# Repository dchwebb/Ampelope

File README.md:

# Ampelope

Overview
--------

Ampelope is a four-channel combined envelope and VCA Eurorack module incorporating a tremolo effect. Each channel can be switched between a fast envelope time, a slow envelope time or a slow envelope with a sine tremolo modulating volume.

The envelopes are loosely modelled on an analog envelope (Roland System 100 type circuit) and feature analog correct capacitor charge/discharge characteristics.

Channels 1 and 2 share the same Attack/Decay/Sustain/Release (ADSR) controls, as do channels 3 and 4. This makes the module particularly suited to dual stereo operation. However each channel has its own gate control allowing independent control of four signals.

The gate controls are normalled in a cascade configuration. For example in dual stereo use gate 1 will be normalled to gate 2 and then a separate gate applied to channel 3 will control channels 3 and 4. In addition gate 1 is normalled to the Doepfer standard gate signal on the 16 pin Eurorack header.

The tremolo control can be clocked or free-run. When clocked the Tremolo potentiometer sets the speed of the tremolo to a multiple of the clock. The tremolo effect applies a sine wave modulation to the envelope.

In addition to the envlopes internal connection to the VCA, envelopes 1 and 3 are available on the front panel and envelopes 2 and 4 on a pin header on the back.

Technical
---------

The module is controlled by an STM32G431 microcontroller which contains four 12-bit DACs. These are used to generate the four envelopes.

The MCU runs at 170MHz and the envelopes samples are generated at 48kHz. The front panel potentiometers are digitised using the MCU's internal ADC. The MCU features a hardware CORDIC peripheral which is used to generate the exponential curves used to model an analog envelopes capacitor charge/discharge characteristics. The CORDIC co-processor is also used to generate the tremolo sine wave.

The MCU's USB peripheral is also connected on the reverse for configuration and upgrade purposes.

The VCA used is an Alpha AS3364 quad linear VCA IC (https://www.alfarzpp.lv/eng/sc/AS3364.php). The MCU outputs the envelopes via its internal DACs at 0V to 3.3V range. This is scaled to 0V to 2V which is the VCA fully closed/fully open range. The envelopes are also amplified to 0V to 8V for control of external modules.

Three TL074 op-amps handle buffering and amplification. NPN transistors provide voltage limiting to incoming gates. The power supply uses a linear regulator to generate the 3.3V digital and analog voltages used by the MCU.

Construction
------------

The module uses a 3 stacked PCB configuration. The components sit on a 4-layer daughter board connected with headers to the 2 layer control PCB holding the LEDs, potentiometers, switches and sockets. This is then bolted to the front panel, also constructed as a 2 layer PCB.

All schematic and PCB layout carried out in Kicad version 5.99.

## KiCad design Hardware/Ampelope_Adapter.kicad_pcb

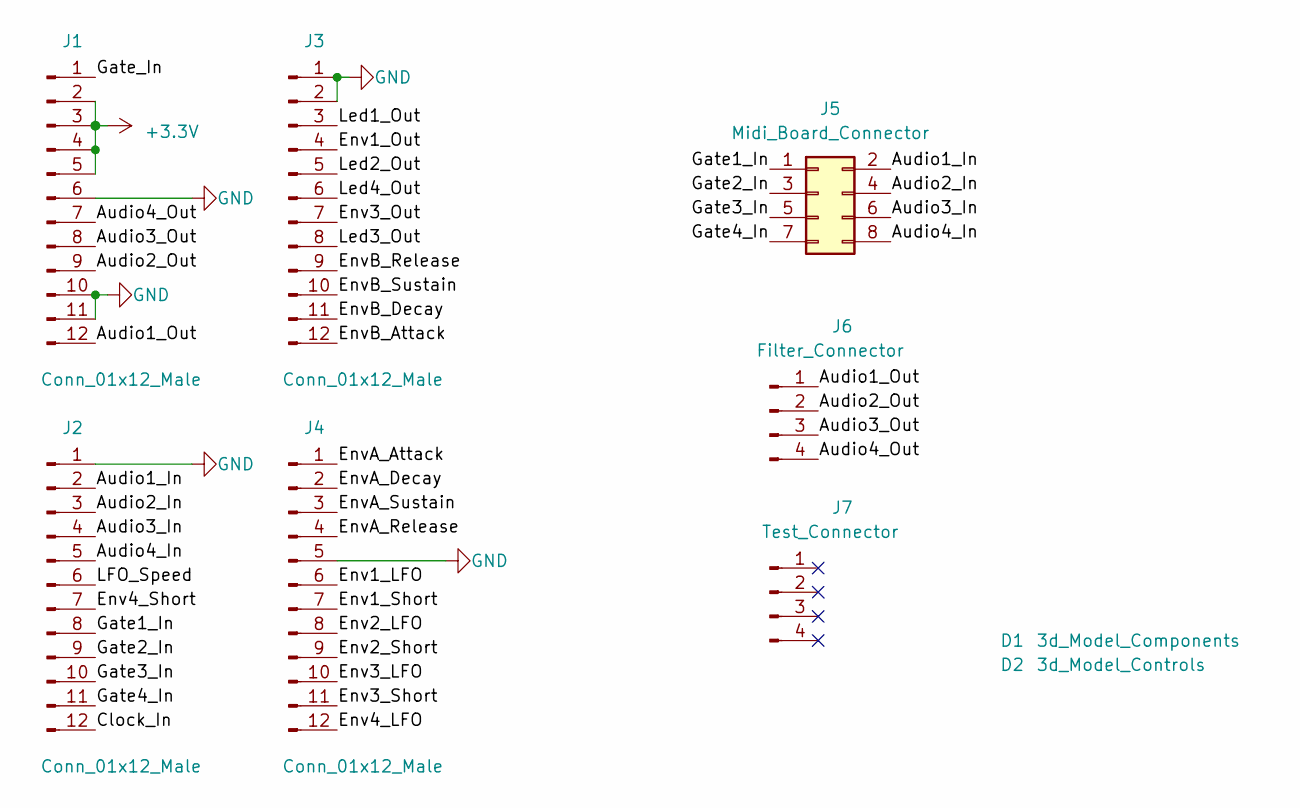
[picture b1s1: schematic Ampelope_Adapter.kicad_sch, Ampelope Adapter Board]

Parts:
D1: 3d_Model_Components; 3D_Dummy
D2: 3d_Model_Controls; 3D_Dummy
J1, J2, J3, J4: Conn_01x12_Male; PinSocket_1x12_P2.54mm_Vertical
J5: Midi_Board_Connector; PinHeader_2x04_P2.54mm_Vertical
J6: Filter_Connector; PinHeader_1x04_P2.54mm_Vertical
J7: Test_Connector; PinHeader_1x04_P2.54mm_Vertical

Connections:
+3V3: J1.2, J1.3, J1.4, J1.5
/Audio1_In: J2.2, J5.2
/Audio1_Out: J1.12, J6.1
/Audio2_In: J2.3, J5.4
/Audio2_Out: J1.9, J6.2
/Audio3_In: J2.4, J5.6
/Audio3_Out: J1.8, J6.3
/Audio4_In: J2.5, J5.8
/Audio4_Out: J1.7, J6.4
/Clock_In: J2.12
/Env1_LFO: J4.6
/Env1_Out: J3.4
/Env1_Short: J4.7
/Env2_LFO: J4.8
/Env2_Short: J4.9
/Env3_LFO: J4.10
/Env3_Out: J3.7
/Env3_Short: J4.11
/Env4_LFO: J4.12
/Env4_Short: J2.7
/EnvA_Attack: J4.1
/EnvA_Decay: J4.2
/EnvA_Release: J4.4
/EnvA_Sustain: J4.3
/EnvB_Attack: J3.12
/EnvB_Decay: J3.11
/EnvB_Release: J3.9
/EnvB_Sustain: J3.10
/Gate1_In: J2.8, J5.1
/Gate2_In: J2.9, J5.3
/Gate3_In: J2.10, J5.5
/Gate4_In: J2.11, J5.7
/Gate_In: J1.1
/LFO_Speed: J2.6
/Led1_Out: J3.3
/Led2_Out: J3.5
/Led3_Out: J3.8
/Led4_Out: J3.6
GND: J1.6, J1.10, J1.11, J2.1, J3.1, J3.2, J4.5

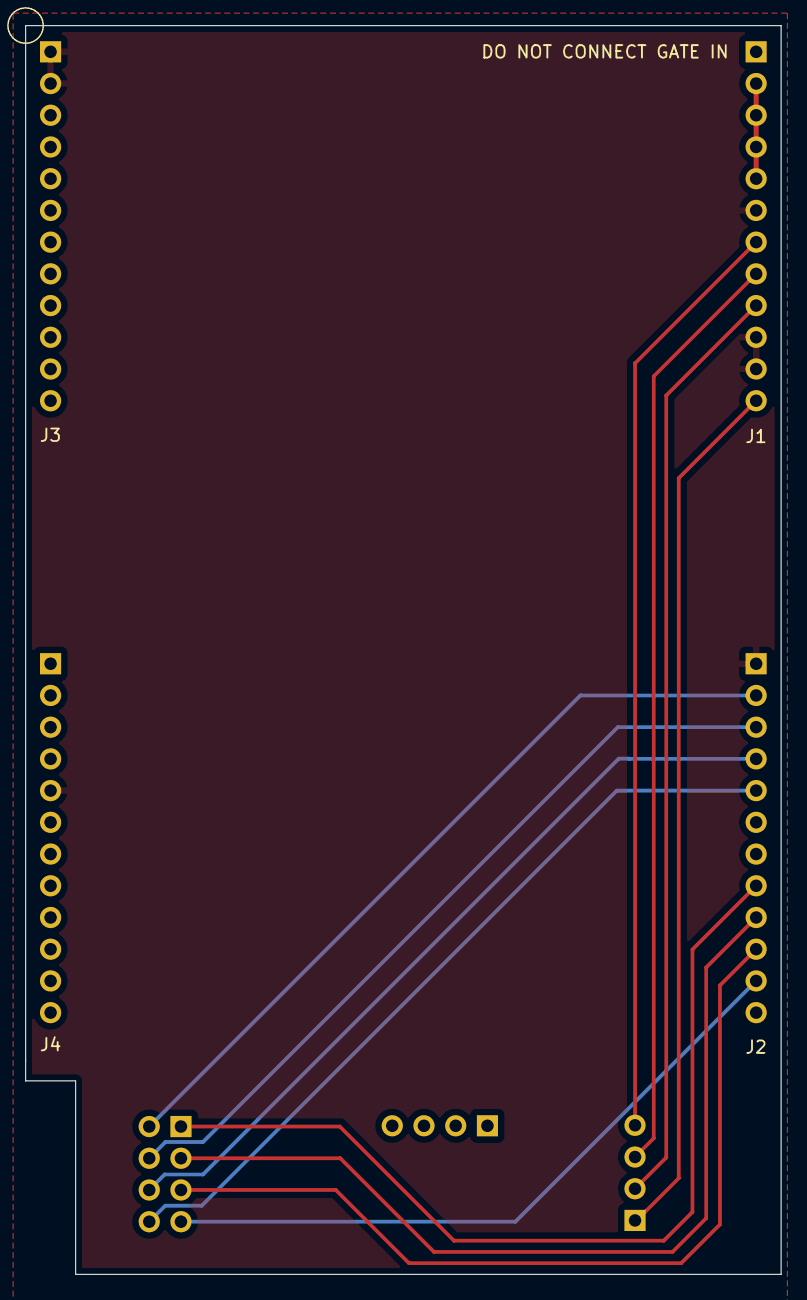
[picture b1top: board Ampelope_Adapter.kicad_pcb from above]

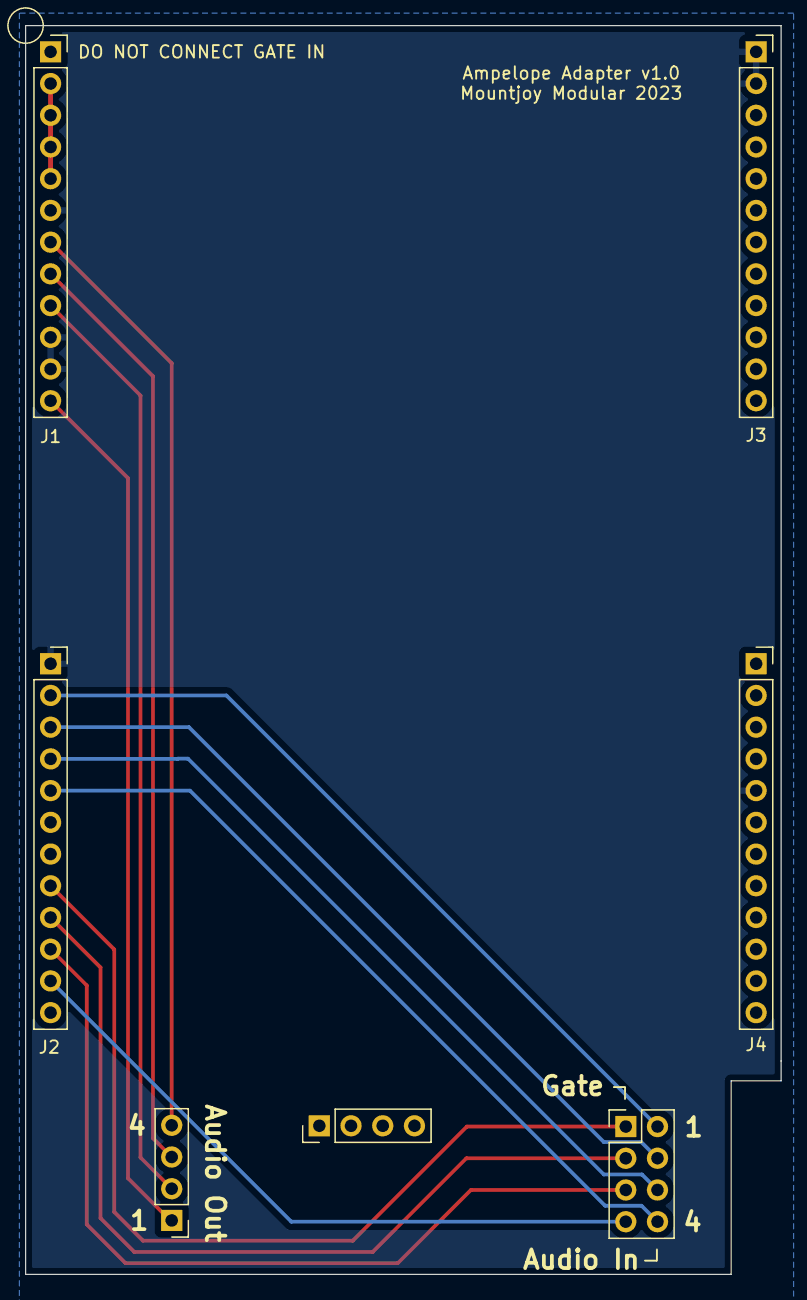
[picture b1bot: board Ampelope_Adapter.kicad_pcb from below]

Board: 2 copper layers, 60.5 x 100.0 mm, 9 parts (8 on the bottom side), 14 nets.

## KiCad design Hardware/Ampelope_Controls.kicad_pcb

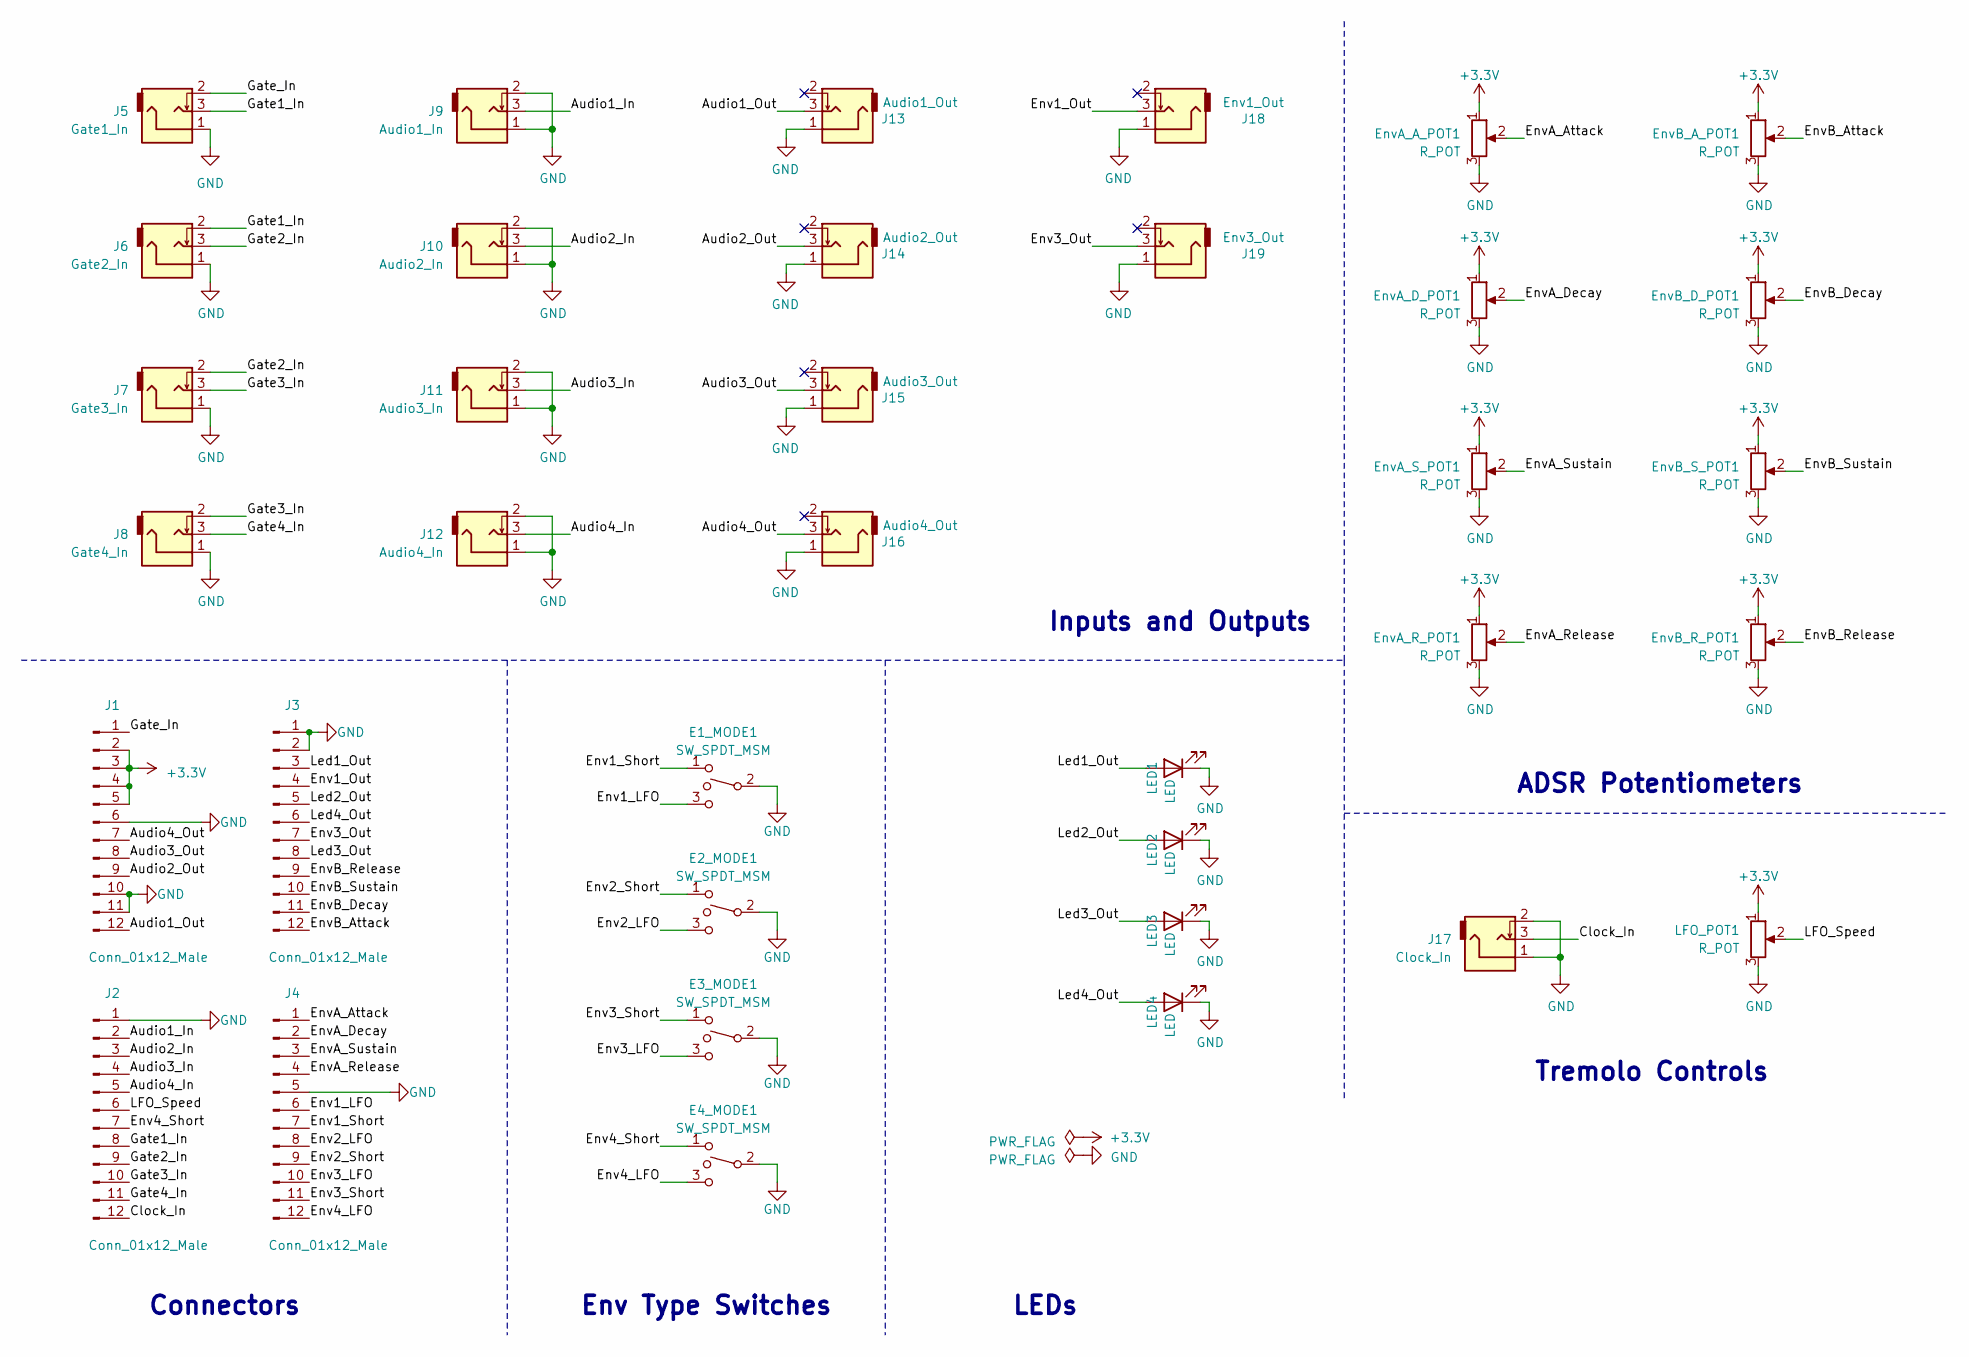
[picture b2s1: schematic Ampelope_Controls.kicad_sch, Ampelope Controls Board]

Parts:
E1_MODE1, E2_MODE1, E3_MODE1, E4_MODE1: SW_SPDT_MSM; SPDT_SubMiniature_Aligned
EnvA_A_POT1: R_POT; Alpha_9mm_Potentiometer_Aligned
EnvA_D_POT1: R_POT; Alpha_9mm_Potentiometer_Aligned
EnvA_R_POT1: R_POT; Alpha_9mm_Potentiometer_Aligned
EnvA_S_POT1: R_POT; Alpha_9mm_Potentiometer_Aligned
EnvB_A_POT1: R_POT; Alpha_9mm_Potentiometer_Aligned
EnvB_D_POT1: R_POT; Alpha_9mm_Potentiometer_Aligned
EnvB_R_POT1: R_POT; Alpha_9mm_Potentiometer_Aligned
EnvB_S_POT1: R_POT; Alpha_9mm_Potentiometer_Aligned
J1, J2, J3, J4: Conn_01x12_Male; PinHeader_1x12_P2.54mm_Vertical
J5: Gate1_In; THONKICONN_hole
J6: Gate2_In; THONKICONN_hole
J7: Gate3_In; THONKICONN_hole
J8: Gate4_In; THONKICONN_hole
J9: Audio1_In; THONKICONN_hole
J10: Audio2_In; THONKICONN_hole
J11: Audio3_In; THONKICONN_hole
J12: Audio4_In; THONKICONN_hole
J13: Audio1_Out; THONKICONN_hole
J14: Audio2_Out; THONKICONN_hole
J15: Audio3_Out; THONKICONN_hole
J16: Audio4_Out; THONKICONN_hole
J17: Clock_In; THONKICONN_hole
J18: Env1_Out; THONKICONN_hole
J19: Env3_Out; THONKICONN_hole
LED1, LED2, LED3, LED4: LED; LED_D3.0mm
LFO_POT1: R_POT; Alpha_9mm_Potentiometer_Aligned

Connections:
+3V3: EnvA_A_POT1.1, EnvA_D_POT1.1, EnvA_R_POT1.1, EnvA_S_POT1.1, EnvB_A_POT1.1, EnvB_D_POT1.1, EnvB_R_POT1.1, EnvB_S_POT1.1, J1.2, J1.3, J1.4, J1.5, LFO_POT1.1
/Audio1_In: J2.2, J9.3
/Audio1_Out: J1.12, J13.3
/Audio2_In: J2.3, J10.3
/Audio2_Out: J1.9, J14.3
/Audio3_In: J2.4, J11.3
/Audio3_Out: J1.8, J15.3
/Audio4_In: J2.5, J12.3
/Audio4_Out: J1.7, J16.3
/Clock_In: J2.12, J17.3
/Env1_LFO: E1_MODE1.3, J4.6
/Env1_Out: J3.4, J18.3
/Env1_Short: E1_MODE1.1, J4.7
/Env2_LFO: E2_MODE1.3, J4.8
/Env2_Short: E2_MODE1.1, J4.9
/Env3_LFO: E3_MODE1.3, J4.10
/Env3_Out: J3.7, J19.3
/Env3_Short: E3_MODE1.1, J4.11
/Env4_LFO: E4_MODE1.3, J4.12
/Env4_Short: E4_MODE1.1, J2.7
/EnvA_Attack: EnvA_A_POT1.2, J4.1
/EnvA_Decay: EnvA_D_POT1.2, J4.2
/EnvA_Release: EnvA_R_POT1.2, J4.4
/EnvA_Sustain: EnvA_S_POT1.2, J4.3
/EnvB_Attack: EnvB_A_POT1.2, J3.12
/EnvB_Decay: EnvB_D_POT1.2, J3.11
/EnvB_Release: EnvB_R_POT1.2, J3.9
/EnvB_Sustain: EnvB_S_POT1.2, J3.10
/Gate1_In: J2.8, J5.3, J6.2
/Gate2_In: J2.9, J6.3, J7.2
/Gate3_In: J2.10, J7.3, J8.2
/Gate4_In: J2.11, J8.3
/Gate_In: J1.1, J5.2
/LFO_Speed: J2.6, LFO_POT1.2
/Led1_Out: J3.3, LED1.2 (A)
/Led2_Out: J3.5, LED2.2 (A)
/Led3_Out: J3.8, LED3.2 (A)
/Led4_Out: J3.6, LED4.2 (A)
GND: E1_MODE1.2, E2_MODE1.2, E3_MODE1.2, E4_MODE1.2, EnvA_A_POT1.3, EnvA_D_POT1.3, EnvA_R_POT1.3, EnvA_S_POT1.3, EnvB_A_POT1.3, EnvB_D_POT1.3, EnvB_R_POT1.3, EnvB_S_POT1.3, J1.6, J1.10, J1.11, J2.1, J3.1, J3.2, J4.5, J5.1, J6.1, J7.1, J8.1, J9.1, J9.2, J10.1, J10.2, J11.1, J11.2, J12.1, J12.2, J13.1, J14.1, J15.1, J16.1, J17.1, J17.2, J18.1, J19.1, LED1.1 (K), LED2.1 (K), LED3.1 (K), LED4.1 (K), LFO_POT1.3

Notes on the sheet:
Connectors
Env Type Switches
LEDs
Inputs and Outputs
ADSR Potentiometers
Tremolo Controls

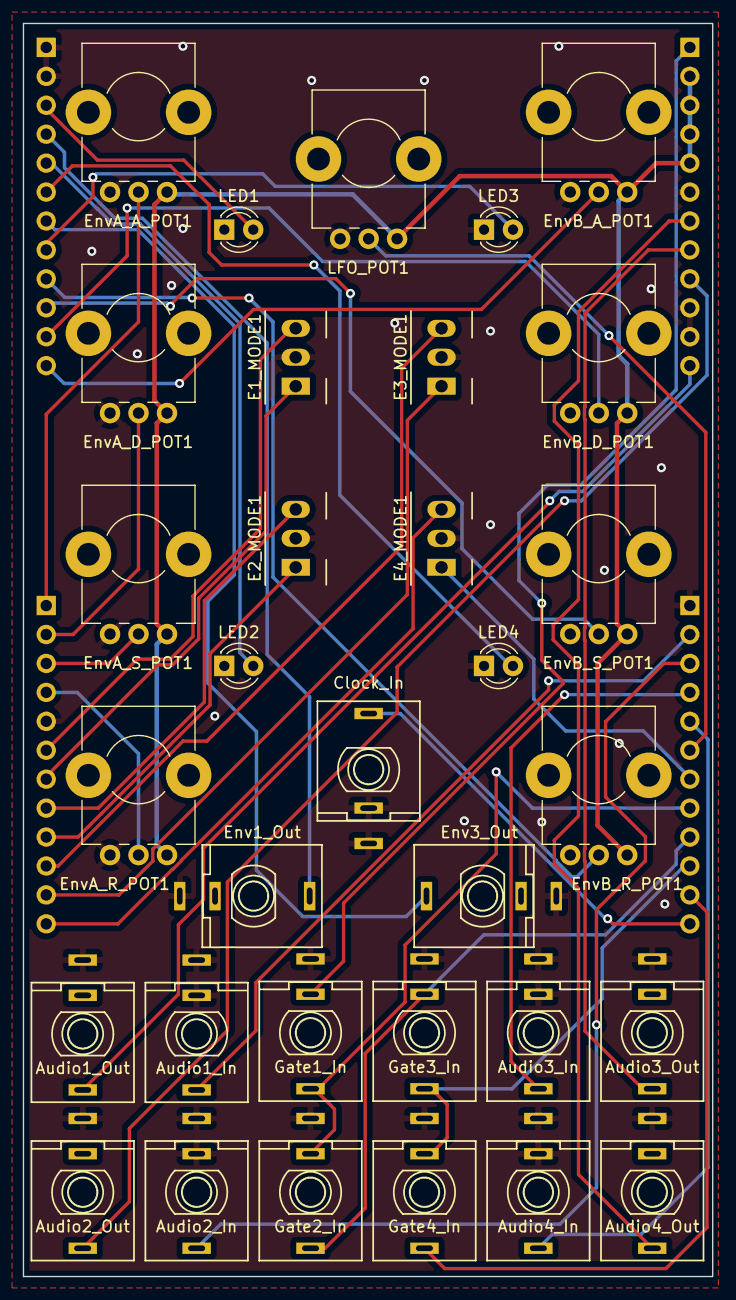
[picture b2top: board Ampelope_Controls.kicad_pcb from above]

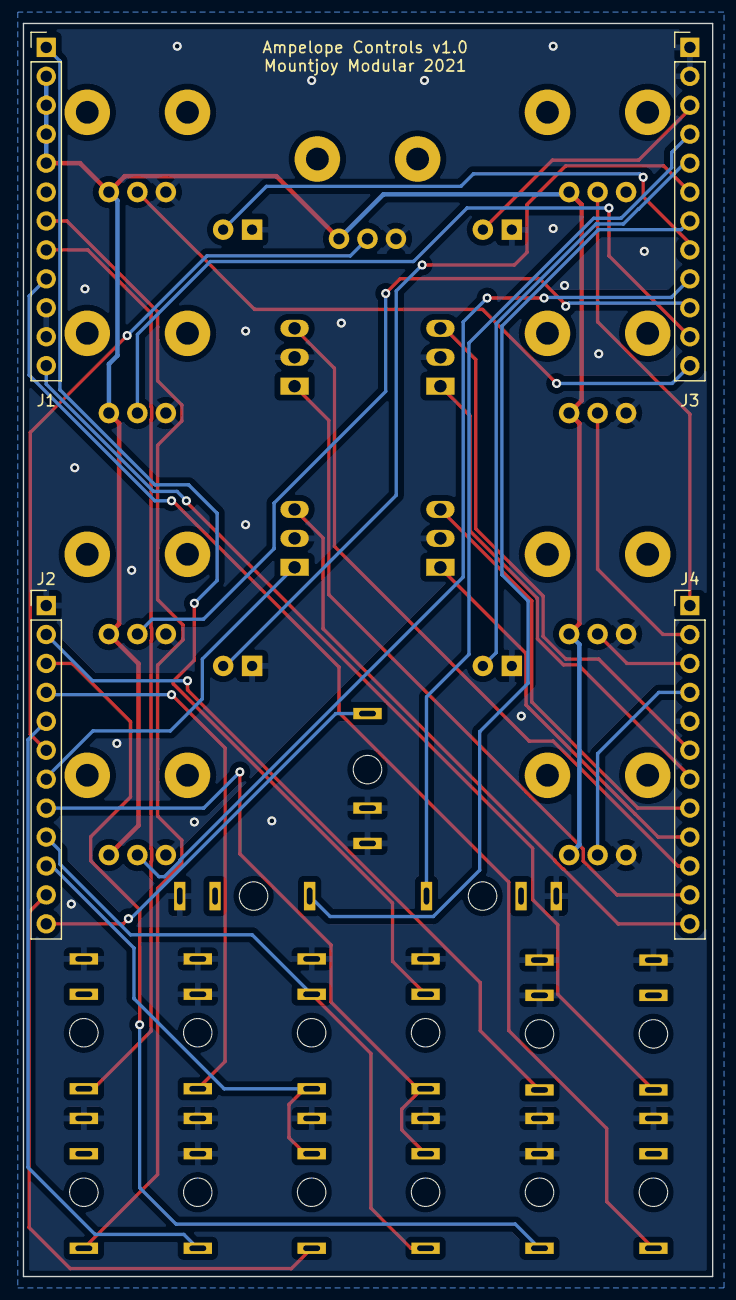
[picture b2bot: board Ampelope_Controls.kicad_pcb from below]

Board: 2 copper layers, 60.5 x 110.0 mm, 36 parts (4 on the bottom side), 39 nets.

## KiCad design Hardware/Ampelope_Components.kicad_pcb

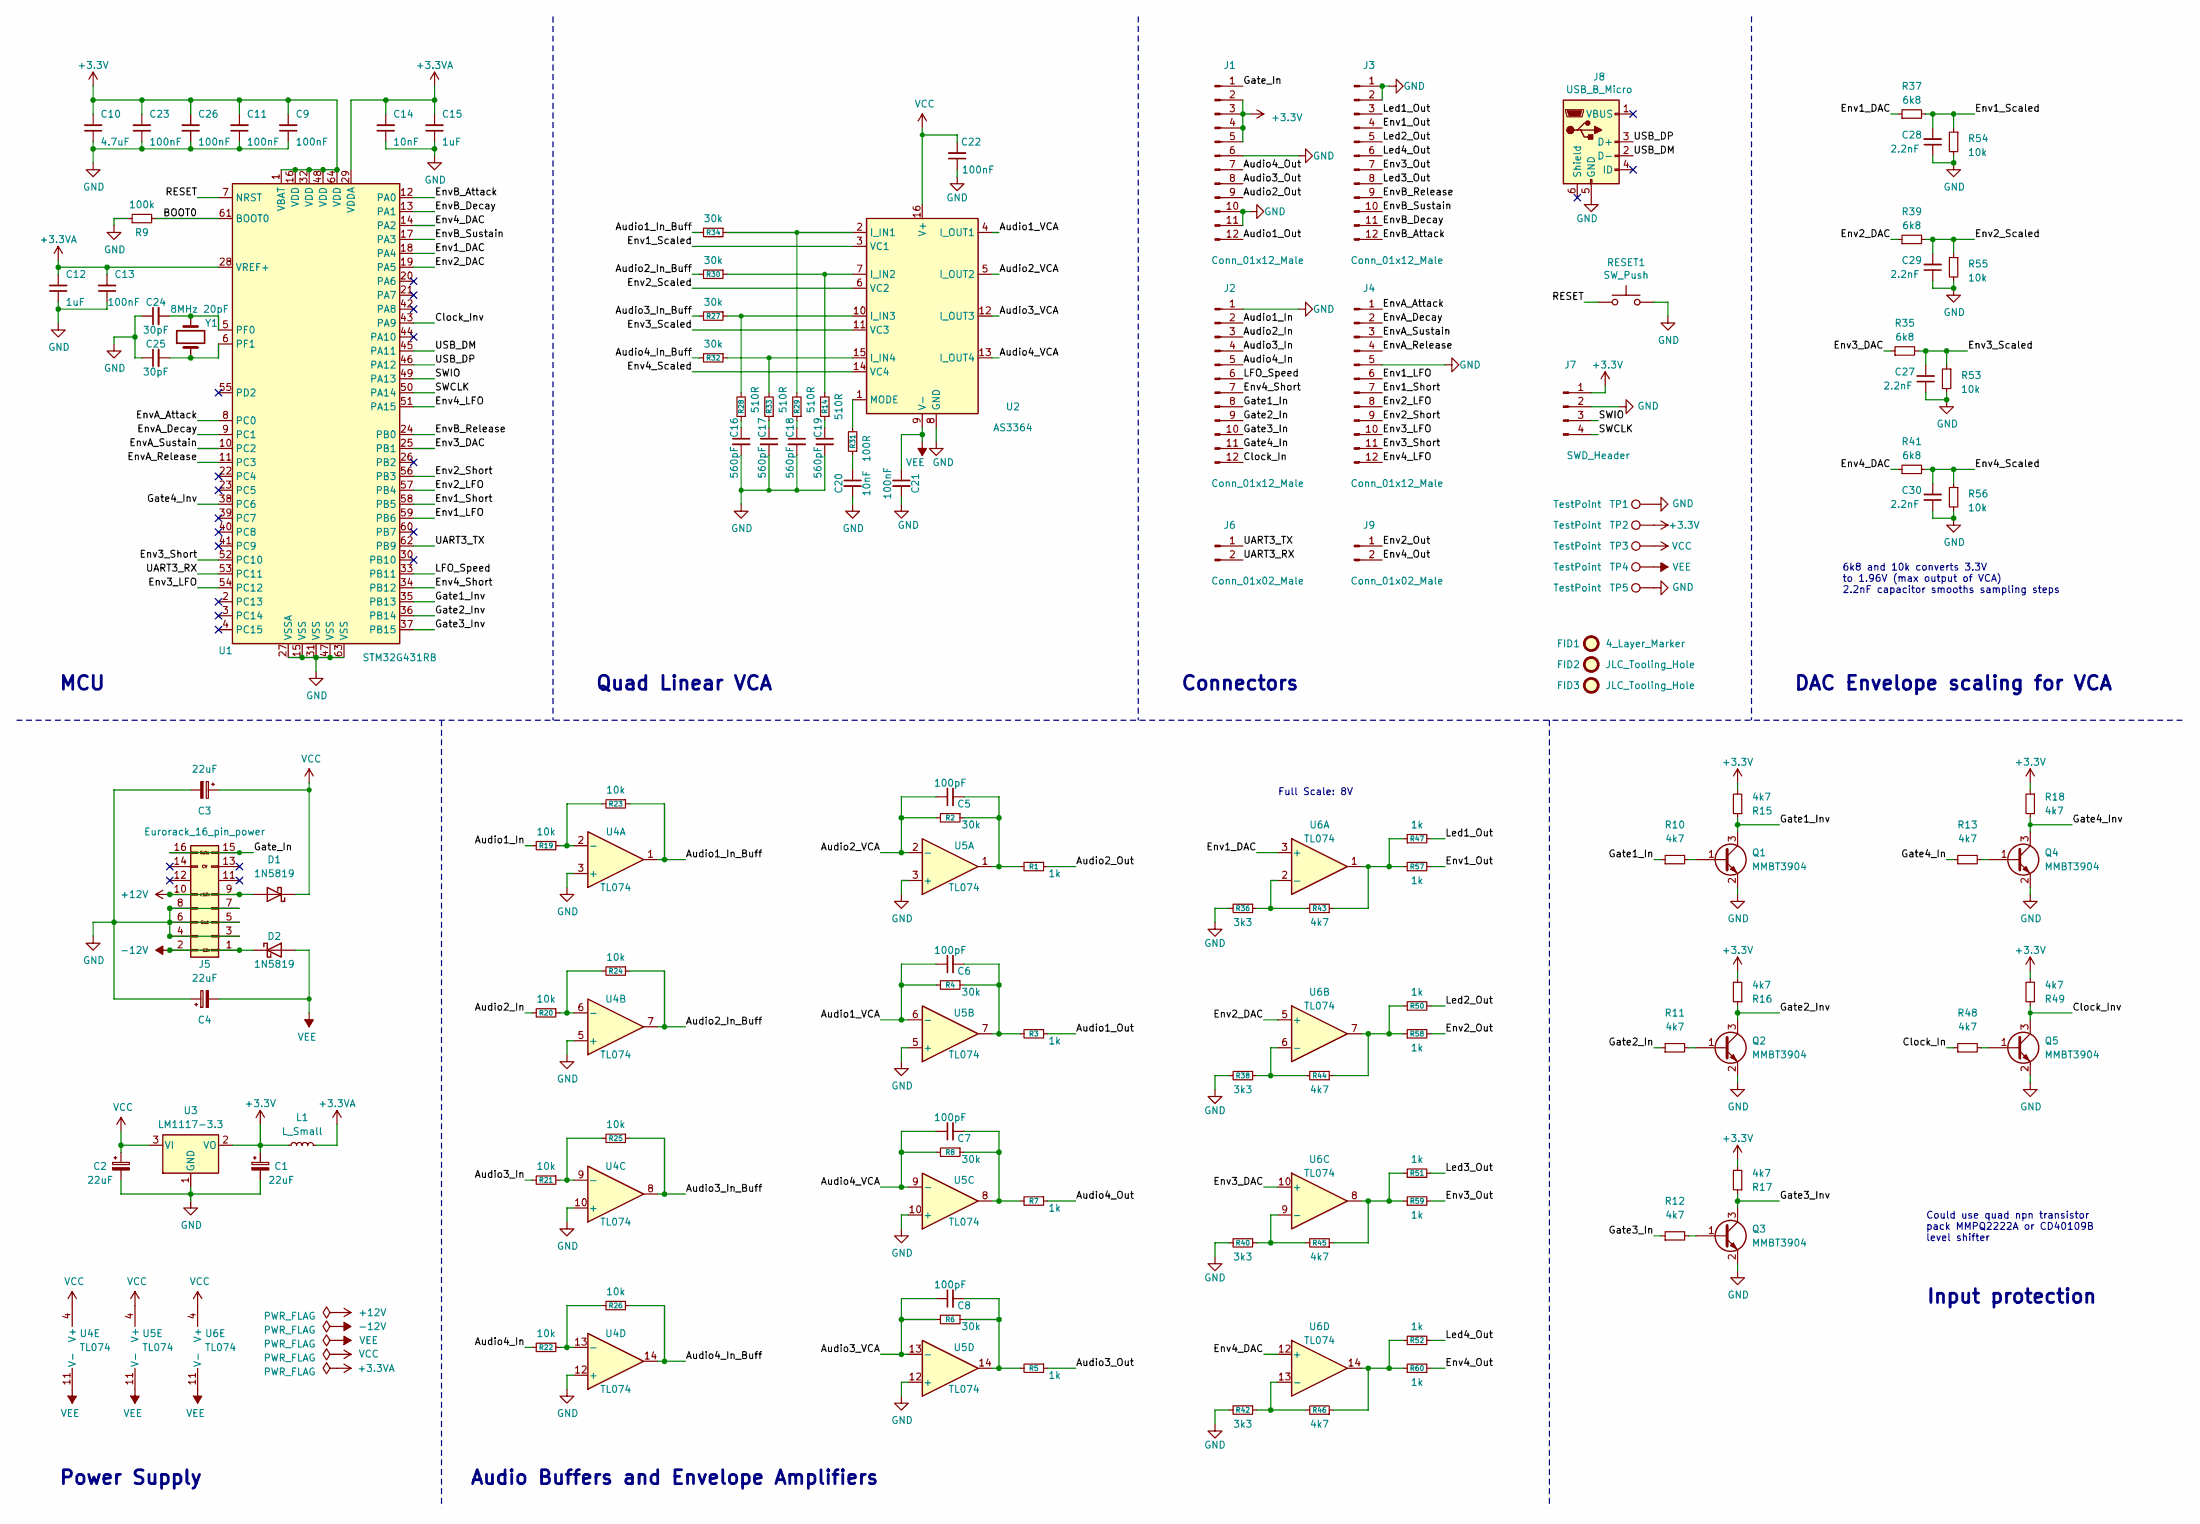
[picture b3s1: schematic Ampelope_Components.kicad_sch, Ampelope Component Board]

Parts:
C1, C2, C3, C4: 22uF; CP_Elec_4x5.8
C5, C6, C7, C8: 100pF; C_0603_1608Metric_Pad1.08x0.95mm_HandSolder; Part_Number C14858
C9, C11, C13, C21, C22, C23, C26: 100nF; C_0603_1608Metric_Pad1.08x0.95mm_HandSolder; Part_Number C14663
C10: 4.7uF; C_0603_1608Metric_Pad1.08x0.95mm_HandSolder; Part_Number C19666
C12, C15: 1uF; C_0603_1608Metric_Pad1.08x0.95mm_HandSolder; Part_Number C15849
C14, C20: 10nF; C_0603_1608Metric_Pad1.08x0.95mm_HandSolder; Part_Number C57112
C16, C17, C18, C19: 560pF; C_0603_1608Metric_Pad1.08x0.95mm_HandSolder
C24, C25: 30pF; C_0603_1608Metric_Pad1.08x0.95mm_HandSolder; Part_Number C22397
C27, C28, C29, C30: 2.2nF; C_0603_1608Metric_Pad1.08x0.95mm_HandSolder; Part_Number C1604
D1, D2: 1N5819; D_SOD-123
FID1: 4_Layer_Marker; 4_Layer_Markers
FID2, FID3: JLC_Tooling_Hole; JLC_SMT_Tooling_Hole
J1, J2, J3, J4: Conn_01x12_Male; PinHeader_1x12_P2.54mm_Vertical
J5: Eurorack_16_pin_power; Eurorack_16_pin_header
J6, J9: Conn_01x02_Male; PinHeader_1x02_P2.54mm_Vertical
J7: SWD_Header; SWD_header
J8: USB_B_Micro; USB_Micro-B_Amphenol
L1: L_Small; L_0805_2012Metric_Pad1.05x1.20mm_HandSolder; Part_Number C1046
Q1, Q2, Q3, Q4, Q5: MMBT3904; SOT-23; Part_Number C20526
R1, R3, R5, R7, R47, R50, R51, R52, R57, R58, R59, R60: 1k; R_0603_1608Metric_Pad0.98x0.95mm_HandSolder; Part_Number C21190
R2, R4, R6, R8, R27, R30, R32, R34: 30k; R_0603_1608Metric_Pad0.98x0.95mm_HandSolder; Part_Number C22984
R9: 100k; R_0603_1608Metric_Pad0.98x0.95mm_HandSolder; Part_Number C25803
R10, R11, R12, R13, R15, R16, R17, R18, R43, R44, R45, R46, R48, R49: 4k7; R_0603_1608Metric_Pad0.98x0.95mm_HandSolder; Part_Number C23162
R14, R28, R29, R33: 510R; R_0603_1608Metric_Pad0.98x0.95mm_HandSolder; Part_Number C23193
R19, R20, R21, R22, R23, R24, R25, R26, R53, R54, R55, R56: 10k; R_0603_1608Metric_Pad0.98x0.95mm_HandSolder; Part_Number C25804
R31: 100R; R_0603_1608Metric_Pad0.98x0.95mm_HandSolder; Part_Number C22775
R35, R37, R39, R41: 6k8; R_0603_1608Metric_Pad0.98x0.95mm_HandSolder; Part_Number C23212
R36, R38, R40, R42: 3k3; R_0603_1608Metric_Pad0.98x0.95mm_HandSolder; Part_Number C22978
RESET1: SW_Push; SW_SPST_EVQQ2
TP1, TP2, TP3, TP4, TP5: TestPoint; 1.3mm_Test_Point
U1: STM32G431RB; LQFP-64_10x10mm_P0.5mm
U2: AS3364; SOIC-16_3.9x9.9mm_P1.27mm
U3: LM1117-3.3; SOT-223-3_TabPin2
U4, U5, U6: TL074; SOIC-14_3.9x8.7mm_P1.27mm
Y1: 8MHz 20pF; Crystal_SMD_0603-2Pin_6.0x3.5mm; Part_Number C115962

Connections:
+3.3VA: C12.2, C13.2, C14.2, C15.2, L1.2, U1.28 (VREF+), U1.29 (VDDA)
+3V3: C1.1, C9.2, C10.2, C11.2, C23.2, C26.2, J1.2, J1.3, J1.4, J1.5, J7.1, L1.1, R15.2, R16.2, R17.2, R18.1, R49.2, TP2.1, U1.1 (VBAT), U1.16 (VDD), U1.32 (VDD), U1.48 (VDD), U1.64 (VDD), U3.2 (VO)
+12V: D1.2 (A), J5.9, J5.10
-12V: D2.1 (K), J5.1, J5.2
/Audio1_In: J2.2, R19.2
/Audio1_In_Buff: R23.1, R34.2, U4.1
/Audio1_Out: J1.12, R3.1
/Audio1_VCA: C6.1, R4.2, U2.4 (I_OUT1), U5.6 (-)
/Audio2_In: J2.3, R20.2
/Audio2_In_Buff: R24.1, R30.2, U4.7
/Audio2_Out: J1.9, R1.1
/Audio2_VCA: C5.1, R2.2, U2.5 (I_OUT2), U5.2 (-)
/Audio3_In: J2.4, R21.2
/Audio3_In_Buff: R25.1, R27.2, U4.8
/Audio3_Out: J1.8, R5.1
/Audio3_VCA: C8.1, R6.2, U2.12 (I_OUT3), U5.13 (-)
/Audio4_In: J2.5, R22.2
/Audio4_In_Buff: R26.1, R32.2, U4.14
/Audio4_Out: J1.7, R7.1
/Audio4_VCA: C7.1, R8.2, U2.13 (I_OUT4), U5.9 (-)
/BOOT0: R9.2, U1.61 (BOOT0)
/Clock_In: J2.12, R48.1
/Clock_Inv: Q5.3 (C), R49.1, U1.43 (PA9)
/Env1_DAC: R37.1, U1.18 (PA4), U6.3 (+)
/Env1_LFO: J4.6, U1.59 (PB6)
/Env1_Out: J3.4, R57.2
/Env1_Scaled: C28.2, R37.2, R54.1, U2.3 (VC1)
/Env1_Short: J4.7, U1.58 (PB5)
/Env2_DAC: R39.1, U1.19 (PA5), U6.5 (+)
/Env2_LFO: J4.8, U1.57 (PB4)
/Env2_Out: J9.1, R58.2
/Env2_Scaled: C29.2, R39.2, R55.1, U2.6 (VC2)
/Env2_Short: J4.9, U1.56 (PB3)
/Env3_DAC: R35.1, U1.25 (PB1), U6.10 (+)
/Env3_LFO: J4.10, U1.54 (PC12)
/Env3_Out: J3.7, R59.2
/Env3_Scaled: C27.2, R35.2, R53.1, U2.11 (VC3)
/Env3_Short: J4.11, U1.52 (PC10)
/Env4_DAC: R41.1, U1.14 (PA2), U6.12 (+)
/Env4_LFO: J4.12, U1.51 (PA15)
/Env4_Out: J9.2, R60.2
/Env4_Scaled: C30.2, R41.2, R56.1, U2.14 (VC4)
/Env4_Short: J2.7, U1.34 (PB12)
/EnvA_Attack: J4.1, U1.8 (PC0)
/EnvA_Decay: J4.2, U1.9 (PC1)
/EnvA_Release: J4.4, U1.11 (PC3)
/EnvA_Sustain: J4.3, U1.10 (PC2)
/EnvB_Attack: J3.12, U1.12 (PA0)
/EnvB_Decay: J3.11, U1.13 (PA1)
/EnvB_Release: J3.9, U1.24 (PB0)
/EnvB_Sustain: J3.10, U1.17 (PA3)
/Gate1_In: J2.8, R10.1
/Gate1_Inv: Q1.3 (C), R15.1, U1.35 (PB13)
/Gate2_In: J2.9, R11.1
/Gate2_Inv: Q2.3 (C), R16.1, U1.36 (PB14)
/Gate3_In: J2.10, R12.1
/Gate3_Inv: Q3.3 (C), R17.1, U1.37 (PB15)
/Gate4_In: J2.11, R13.1
/Gate4_Inv: Q4.3 (C), R18.2, U1.38 (PC6)
/Gate_In: J1.1, J5.15, J5.16
/LFO_Speed: J2.6, U1.33 (PB11)
/Led1_Out: J3.3, R47.2
/Led2_Out: J3.5, R50.2
/Led3_Out: J3.8, R51.2
/Led4_Out: J3.6, R52.2
/RESET: RESET1.1, U1.7 (NRST)
/SWCLK: J7.4, U1.50 (PA14)
/SWIO: J7.3, U1.49 (PA13)
/UART3_RX: J6.2, U1.53 (PC11)
/UART3_TX: J6.1, U1.62 (PB9)
/USB_DM: J8.2 (D-), U1.45 (PA11)
/USB_DP: J8.3 (D+), U1.46 (PA12)
GND: C1.2, C2.2, C3.2, C4.1, C9.1, C10.1, C11.1, C12.1, C13.1, C14.1, C15.1, C16.2, C17.2, C18.2, C19.2, C20.2, C21.2, C22.1, C23.1, C24.1, C25.1, C26.1, C27.1, C28.1, C29.1, C30.1, J1.6, J1.10, J1.11, J2.1, J3.1, J3.2, J4.5, J5.3, J5.4, J5.5, J5.6, J5.7, J5.8, J7.2, J8.5 (GND), Q1.2 (E), Q2.2 (E), Q3.2 (E), Q4.2 (E), Q5.2 (E), R9.1, R36.2, R38.2, R40.2, R42.2, R53.2, R54.2, R55.2, R56.2, RESET1.2, TP1.1, TP5.1, U1.15 (VSS), U1.27 (VSSA), U1.31 (VSS), U1.47 (VSS), U1.63 (VSS), U2.8 (GND), U3.1 (GND), U4.3 (+), U4.5 (+), U4.10 (+), U4.12 (+), U5.3 (+), U5.5 (+), U5.10 (+), U5.12 (+)
unnamed: C5.2, R1.2, R2.1, U5.1
unnamed: C6.2, R3.2, R4.1, U5.7
unnamed: C7.2, R7.2, R8.1, U5.8
unnamed: C8.2, R5.2, R6.1, U5.14
unnamed: C16.1, R28.1
unnamed: C17.1, R33.1
unnamed: C18.1, R29.1
unnamed: C19.1, R14.1
unnamed: C20.1, R31.1
unnamed: C24.2, U1.5 (PF0), Y1.2
unnamed: C25.2, U1.6 (PF1), Y1.1
unnamed: Q1.1 (B), R10.2
unnamed: Q2.1 (B), R11.2
unnamed: Q3.1 (B), R12.2
unnamed: Q4.1 (B), R13.2
unnamed: Q5.1 (B), R48.2
unnamed: R14.2, R30.1, U2.7 (I_IN2)
unnamed: R19.1, R23.2, U4.2 (-)
unnamed: R20.1, R24.2, U4.6 (-)
unnamed: R21.1, R25.2, U4.9 (-)
unnamed: R22.1, R26.2, U4.13 (-)
unnamed: R27.1, R28.2, U2.10 (I_IN3)
unnamed: R29.2, R34.1, U2.2 (I_IN1)
unnamed: R31.2, U2.1 (MODE)
unnamed: R32.1, R33.2, U2.15 (I_IN4)
unnamed: R36.1, R43.2, U6.2 (-)
unnamed: R38.1, R44.2, U6.6 (-)
unnamed: R40.1, R45.2, U6.9 (-)
unnamed: R42.1, R46.2, U6.13 (-)
unnamed: R43.1, R47.1, R57.1, U6.1
unnamed: R44.1, R50.1, R58.1, U6.7
unnamed: R45.1, R51.1, R59.1, U6.8
unnamed: R46.1, R52.1, R60.1, U6.14
VCC: C2.1, C3.1, C22.2, D1.1 (K), TP3.1, U2.16 (V+), U3.3 (VI), U4.4 (V+), U5.4 (V+), U6.4 (V+)
VEE: C4.2, C21.1, D2.2 (A), TP4.1, U2.9 (V-), U4.11 (V-), U5.11 (V-), U6.11 (V-)

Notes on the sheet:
MCU
Power Supply
Audio Buffers and Envelope Amplifiers
Quad Linear VCA
Connectors
Full Scale: 8V
DAC Envelope scaling for VCA
6k8 and 10k converts 3.3V to 1.96V (max output of VCA) 2.2nF capacitor smooths sampling steps
Could use quad npn transistor pack MMPQ2222A or CD40109B level shifter
Input protection
